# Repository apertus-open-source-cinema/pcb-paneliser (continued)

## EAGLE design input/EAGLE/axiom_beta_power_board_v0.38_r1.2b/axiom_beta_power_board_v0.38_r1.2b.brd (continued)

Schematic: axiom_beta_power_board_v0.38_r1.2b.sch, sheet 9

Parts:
R51, R52, R53, R54, R55, R56, R57, R58, R59, R60, R61, R62: R1206-B; 1206-B
R73: 750R; 0402-B
R74: 1k27; 0402-B
R75: 430R; 0402-B
R76: 0R; 0402-B
R77: 100R; 0402-B
R78: 560R; 0402-B
U17, U18, U19, U20, U23, U24: PAC1720; DFN3X3_10LEAD

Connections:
E_VE: R57.2, U19.2 (SENSE1-); also elsewhere on the board
E_VE': R57.1, U19.1 (SENSE1+); also elsewhere on the board
GND: R73.2, R74.2, R75.2, R76.2, R77.2, R78.2, U17.5 (GND), U17.EPAD (GND), U18.5 (GND), U18.EPAD (GND), U19.5 (GND), U19.EPAD (GND), U20.5 (GND), U20.EPAD (GND), U23.5 (GND), U23.EPAD (GND), U24.5 (GND), U24.EPAD (GND); also elsewhere on the board
unnamed: R73.1, U18.6 (ASEL)
unnamed: R75.1, U24.6 (ASEL)
unnamed: R78.1, U23.6 (ASEL)
unnamed: R74.1, U20.6 (ASEL)
unnamed: R76.1, U19.6 (ASEL)
unnamed: R77.1, U17.6 (ASEL)
N_VE: R54.2, U20.4 (SENSE2-); also elsewhere on the board
N_VE': R54.1, U20.3 (SENSE2+); also elsewhere on the board
N_VN: R53.2, U20.2 (SENSE1-); also elsewhere on the board
N_VN': R53.1, U20.1 (SENSE1+); also elsewhere on the board
N_VW: R52.2, U18.4 (SENSE2-); also elsewhere on the board
N_VW': R52.1, U18.3 (SENSE2+); also elsewhere on the board
PCIE_VCCIO: R61.2, U23.2 (SENSE1-)
PMOD_SCL: U17.9 (SMCLK), U18.9 (SMCLK), U19.9 (SMCLK), U20.9 (SMCLK), U23.9 (SMCLK), U24.9 (SMCLK); also elsewhere on the board
PMOD_SDA: U17.8 (SMDATA), U18.8 (SMDATA), U19.8 (SMDATA), U20.8 (SMDATA), U23.8 (SMDATA), U24.8 (SMDATA); also elsewhere on the board
S_VE: R58.2, U19.4 (SENSE2-); also elsewhere on the board
S_VE': R58.1, U19.3 (SENSE2+); also elsewhere on the board
S_VS: R59.2, U17.2 (SENSE1-); also elsewhere on the board
S_VS': R59.1, U17.1 (SENSE1+); also elsewhere on the board
S_VW: R60.2, U17.4 (SENSE2-); also elsewhere on the board
S_VW': R60.1, U17.3 (SENSE2+); also elsewhere on the board
VCC: U17.10 (VDD), U18.10 (VDD), U19.10 (VDD), U20.10 (VDD), U23.10 (VDD), U24.10 (VDD); also elsewhere on the board
VCCIO: R55.1, R56.1, R61.1, R62.1, U23.1 (SENSE1+), U23.3 (SENSE2+), U24.1 (SENSE1+), U24.3 (SENSE2+); also elsewhere on the board
VCCO_13: R56.2, U24.4 (SENSE2-); also elsewhere on the board
VCCO_34: R62.2, U23.4 (SENSE2-); also elsewhere on the board
VCCO_35: R55.2, U24.2 (SENSE1-); also elsewhere on the board
W_VW: R51.2, U18.2 (SENSE1-); also elsewhere on the board
W_VW': R51.1, U18.1 (SENSE1+); also elsewhere on the board

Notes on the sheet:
AXIOM Beta Power Board
Copyright (C) 2014-2020 H.Poetzl Licensed under CERN OHL v.1.2
Sensor Power Sensing
[0x48]
[0x49]
[0x4B]
[0x4D]
[0x4A]
[0x4C]

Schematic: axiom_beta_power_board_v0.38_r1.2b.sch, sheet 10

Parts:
C49, C52, C55, C58, C61: 4u7; 0603-B
C50, C53, C56, C59, C62: DNP; 0402-B
C51, C54, C57, C60, C63: 10u; 0603-B
C86: 100n; 0402-B
L9, L10, L11, L12, L13: L0805-A; 0805-A
MCN: MCP1727-ADJE/MF; DFN65P300X300X100-9N
MCS: MCP1727-ADJE/MF; DFN65P300X300X100-9N
MXN: MCP1727-ADJE/MF; DFN65P300X300X100-9N
MXS: MCP1727-ADJE/MF; DFN65P300X300X100-9N
R33, R35, R39, R41: RB; 0402-B
R34, R36, R40, R42: RD; 0402-B
R37: 102k; 0402-B
R38: 20k; 0402-B
R67, R68, R69, R70, R71, R72: R1206-B; 1206-B
R81: 2k0; 0402-B
R82: 1k6; 0402-B
R83: 2k7; 0402-B
R90: 15k; 0402-B
R91: 1k; 0402-B
U7: MCP23018-E/MJ; QFN50P400X400X80-25N
U14, U15, U22: PAC1720; DFN3X3_10LEAD
VIO: MCP1727-ADJE/MF; DFN65P300X300X100-9N

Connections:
BETA_5V: R70.1, U22.3 (SENSE2+); also elsewhere on the board
BETA_5V': C51.1, C54.1, C57.1, C60.1, C63.1, MCN.1 (VIN), MCN.2 (VIN), MCS.1 (VIN), MCS.2 (VIN), MXN.1 (VIN), MXN.2 (VIN), MXS.1 (VIN), MXS.2 (VIN), R70.2, U22.4 (SENSE2-), VIO.1 (VIN), VIO.2 (VIN); also elsewhere on the board
CSO_NE_V: R67.2, U14.2 (SENSE1-); also elsewhere on the board
CSO_N_V': L12.2, R67.1, U14.1 (SENSE1+)
CSO_SW_V: R71.2, U15.2 (SENSE1-); also elsewhere on the board
CSO_S_V': L10.2, R71.1, U15.1 (SENSE1+)
GND: C49.2, C50.2, C51.2, C52.2, C53.2, C54.2, C55.2, C56.2, C57.2, C58.2, C59.2, C60.2, C61.2, C62.2, C63.2, C86.2, MCN.4 (GND), MCN.9 (EP), MCS.4 (GND), MCS.9 (EP), MXN.4 (GND), MXN.9 (EP), MXS.4 (GND), MXS.9 (EP), R34.2, R36.2, R38.2, R40.2, R42.2, R81.2, R82.2, R83.2, R91.2, U7.23 (VSS), U7.25 (VSS), U14.5 (GND), U14.EPAD (GND), U15.5 (GND), U15.EPAD (GND), U22.5 (GND), U22.EPAD (GND), VIO.4 (GND), VIO.9 (EP); also elsewhere on the board
MCN_EN: MCN.3 (!SHDN), U7.18 (GPA3)
MCN_PG: MCN.5 (PWRGD), U7.17 (GPA2)
MCS_EN: MCS.3 (!SHDN), U7.22 (GPA7)
MCS_PG: MCS.5 (PWRGD), U7.21 (GPA6)
MXN_EN: MXN.3 (!SHDN), U7.16 (GPA1)
MXN_PG: MXN.5 (PWRGD), U7.15 (GPA0)
MXS_EN: MXS.3 (!SHDN), U7.1 (GPB1)
MXS_PG: MXS.5 (PWRGD), U7.24 (GPB0)
unnamed: C49.1, L9.1, MXS.8 (VOUT), R41.1
unnamed: MXS.7 (ADJ), R41.2, R42.1
unnamed: C50.1, MXS.6 (CDELAY)
unnamed: R81.1, U14.6 (ASEL)
unnamed: R83.1, U15.6 (ASEL)
unnamed: C52.1, L10.1, MCS.8 (VOUT), R39.1
unnamed: MCS.7 (ADJ), R39.2, R40.1
unnamed: C53.1, MCS.6 (CDELAY)
unnamed: R82.1, U22.6 (ASEL)
unnamed: C55.1, L11.1, R37.1, VIO.8 (VOUT)
unnamed: R37.2, R38.1, VIO.7 (ADJ)
unnamed: C56.1, VIO.6 (CDELAY)
unnamed: C58.1, L12.1, MCN.8 (VOUT), R35.1
unnamed: MCN.7 (ADJ), R35.2, R36.1
unnamed: C59.1, MCN.6 (CDELAY)
unnamed: C61.1, L13.1, MXN.8 (VOUT), R33.1
unnamed: MXN.7 (ADJ), R33.2, R34.1
unnamed: C62.1, MXN.6 (CDELAY)
unnamed: R90.2, R91.1, U7.11 (ADDR)
PCIE_N_V: R68.2, U14.4 (SENSE2-); also elsewhere on the board
PCIE_N_V': L13.2, R68.1, U14.3 (SENSE2+)
PCIE_S_V: R72.2, U15.4 (SENSE2-); also elsewhere on the board
PCIE_S_V': L9.2, R72.1, U15.3 (SENSE2+)
PMOD_SCL: U7.9 (SCL), U14.9 (SMCLK), U15.9 (SMCLK), U22.9 (SMCLK); also elsewhere on the board
PMOD_SDA: U7.10 (SDA), U14.8 (SMDATA), U15.8 (SMDATA), U22.8 (SMDATA); also elsewhere on the board
VCC: C86.1, R90.1, U7.8 (VDD), U7.12 (!RESET), U14.10 (VDD), U15.10 (VDD), U22.10 (VDD); also elsewhere on the board
VCCIO: L11.2; also elsewhere on the board
VIO_EN: U7.20 (GPA5), VIO.3 (!SHDN)
VIO_PG: U7.19 (GPA4), VIO.5 (PWRGD)
ZED_5V: R69.1, U22.1 (SENSE1+); also elsewhere on the board
ZED_5V': R69.2, U22.2 (SENSE1-); also elsewhere on the board

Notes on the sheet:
AXIOM Beta Power Board
Copyright (C) 2014-2020 H.Poetzl Licensed under CERN OHL v.1.2
Power, Control and Sensing
[ID=0x20]
[0x29]
[0x28]
[0x2A]
[3V3]
[2V5]

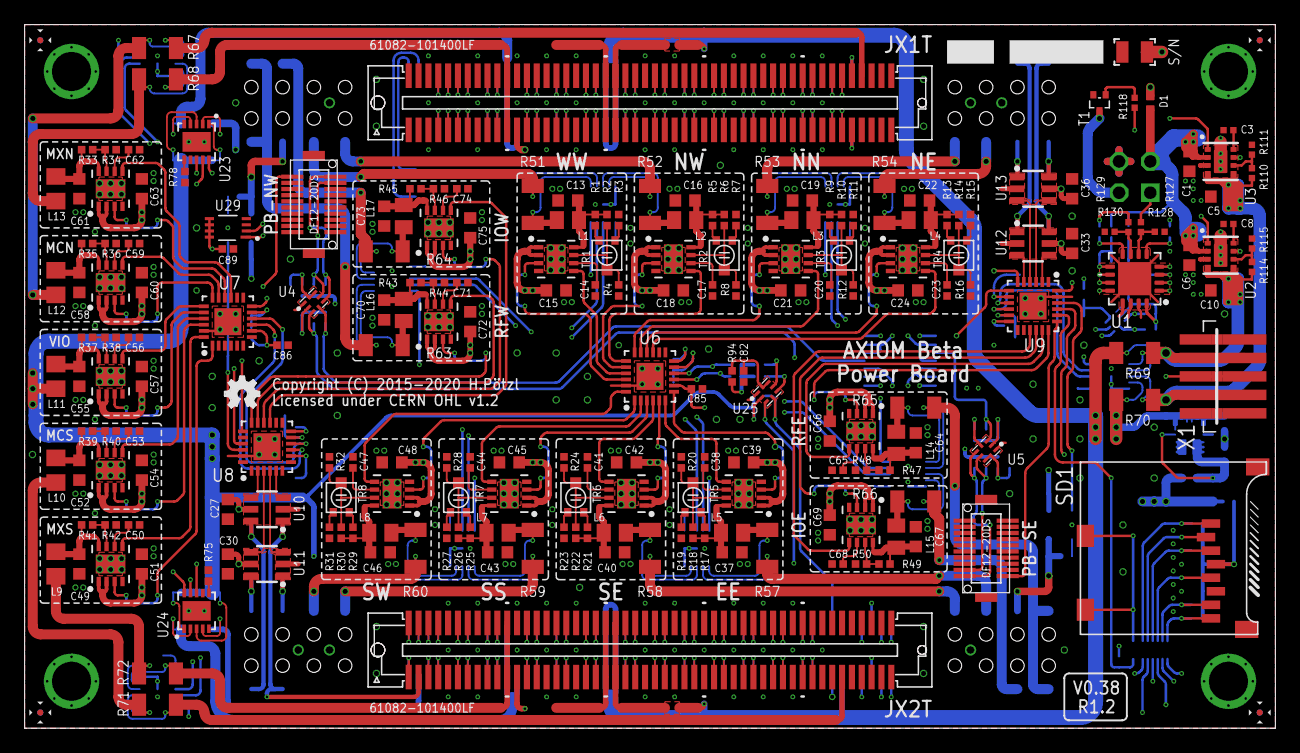
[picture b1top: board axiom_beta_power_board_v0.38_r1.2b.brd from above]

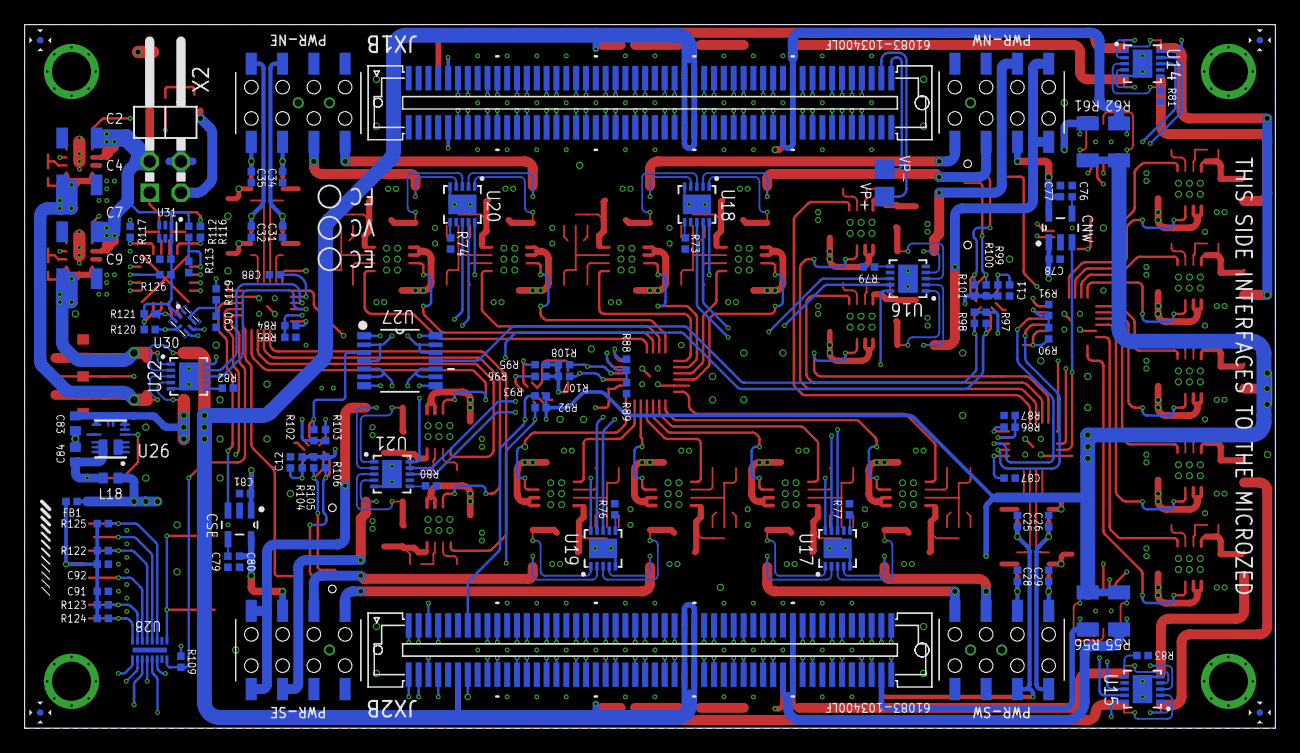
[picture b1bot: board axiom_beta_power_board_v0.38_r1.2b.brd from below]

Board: 4 copper layers, 101.6 x 57.1 mm, 329 parts (110 on the bottom side), 360 nets.

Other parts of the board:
LOGO1: OSHW_LOGO_FILLX0100-NT; OSHW_FILLX100_NOTEXT

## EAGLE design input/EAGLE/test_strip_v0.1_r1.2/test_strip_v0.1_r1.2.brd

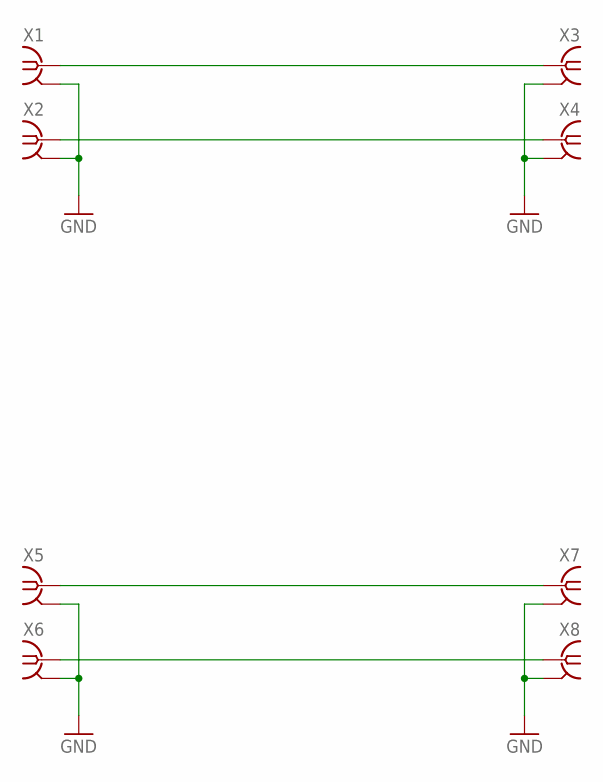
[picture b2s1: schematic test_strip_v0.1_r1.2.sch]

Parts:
X1, X2, X3, X4, X5, X6, X7, X8: BU-SMA-E-ND; SMA-EDGE_ND

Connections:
GND: X1.2@3 (2), X1.2@4 (2), X2.2@3 (2), X2.2@4 (2), X3.2@3 (2), X3.2@4 (2), X4.2@3 (2), X4.2@4 (2), X5.2@3 (2), X5.2@4 (2), X6.2@3 (2), X6.2@4 (2), X7.2@3 (2), X7.2@4 (2), X8.2@3 (2), X8.2@4 (2)
SIGA_N: X2.1, X4.1
SIGA_P: X1.1, X3.1
SIGB_N: X6.1, X8.1
SIGB_P: X5.1, X7.1

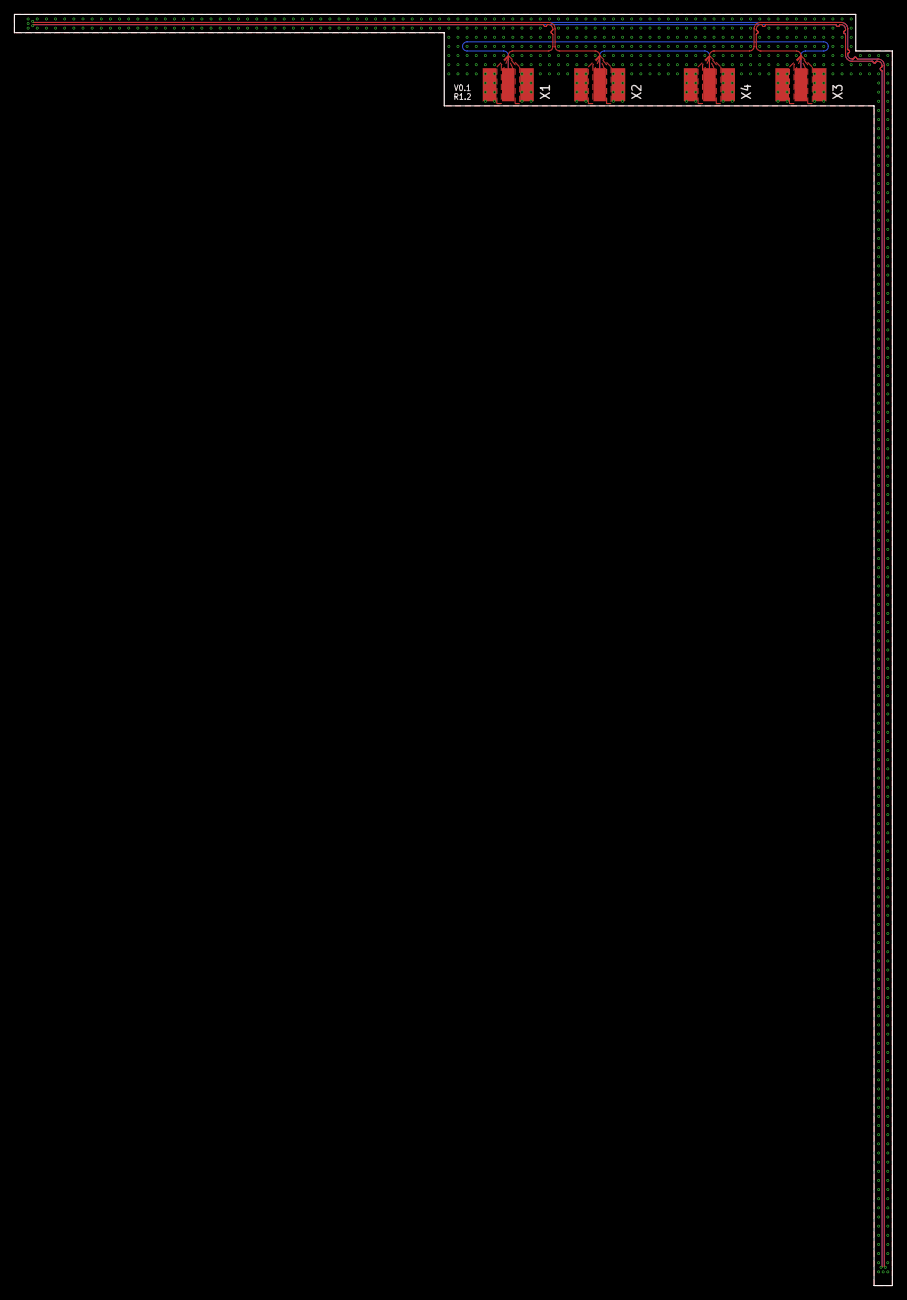
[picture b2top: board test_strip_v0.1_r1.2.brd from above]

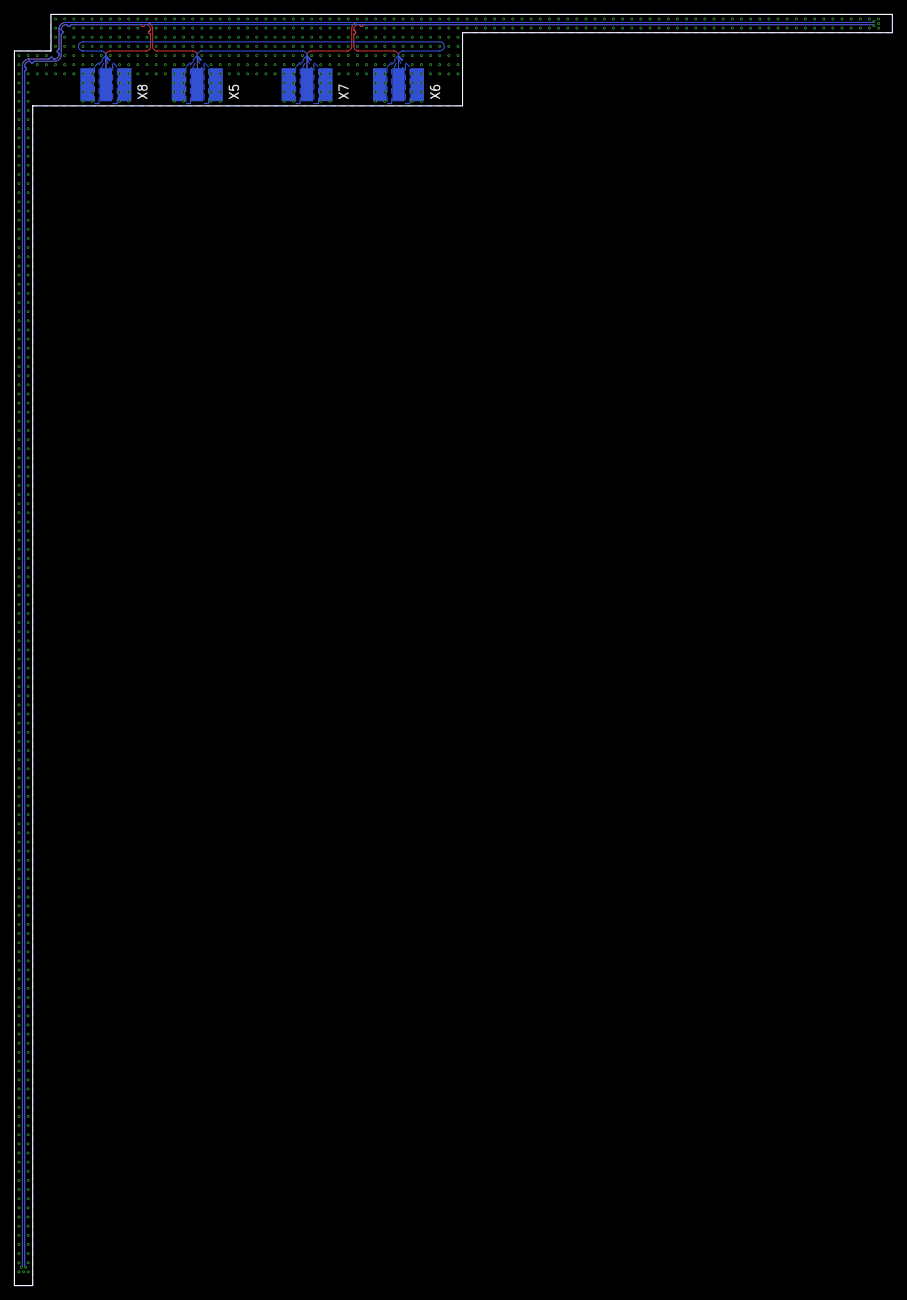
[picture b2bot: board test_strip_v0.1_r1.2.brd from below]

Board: 4 copper layers, 121.9 x 176.5 mm, 8 parts (4 on the bottom side), 5 nets.
